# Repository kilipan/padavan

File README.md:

# Padavan
A Minivan keyboard with small numpad and wireless capabilities.

## Layout Options

An untested southpaw variant can be found in the [`southpaw`](https://github.com/kilipan/padavan/tree/main/southpaw) directory. Use at your own risk!

## BOM
| Amount | Part |
|-------:|:-----|
|      1 | Padavan PCB |
|      1 | Pro-Micro compatible MCU board |
|  58-63 | Kailh MX hot swap sockets |
|      1 | Padavan case and plate |
|     10 | Cylindrical magnets (d=3mm, l=2mm) |
|      5 | M2 screws, l=8mm |
|     11 | M2 screws, l=6mm |
|     16 | M2 heat inserts |

If you want to use the Padavan wirelessly, you'll need a wireless-capable controller, like e.g. the [nice!nano](https://nicekeyboards.com/nice-nano/)!

## Firmware
Tested and working [ZMK firmware](https://github.com/kilipan/zmk-config-padavan) is available,
as well as [QMK firmware including Vial](https://github.com/kilipan/qmk-config-padavan).

## Availability
All files are provided under CERN-OHL-S license. Feel free to build your own!

### Case
The fantastic case was designed by DizzySkizzo (`dizzyskizzo1337` on discord). Thank you for letting me use and open source this genius design!
Production files available in [`production/case`](https://github.com/kilipan/padavan/tree/main/production/case).

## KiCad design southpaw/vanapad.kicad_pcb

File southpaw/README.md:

# Vanapad
A southpaw Minivan keyboard with small numpad and wireless capabilities.

**Untested hardware! Use at your own risk!**

## Layout Options

## BOM
| Amount | Part |
|-------:|:-----|
|      1 | Vanapad PCB |
|      1 | Vanapad plate |
|      1 | Pro-Micro compatible MCU board |
|  58-63 | Kailh MX hot swap sockets |

If you want to use the Vanapad wirelessly, you'll need a wireless-capable controller, like e.g. the [nice!nano](https://nicekeyboards.com/nice-nano/)!

## Firmware
Not yet available. You can try modifying the padavan firmware!

## Availability
All files are provided under CERN-OHL-S license. Feel free to build your own!

### Case
None available as of the time of writing.

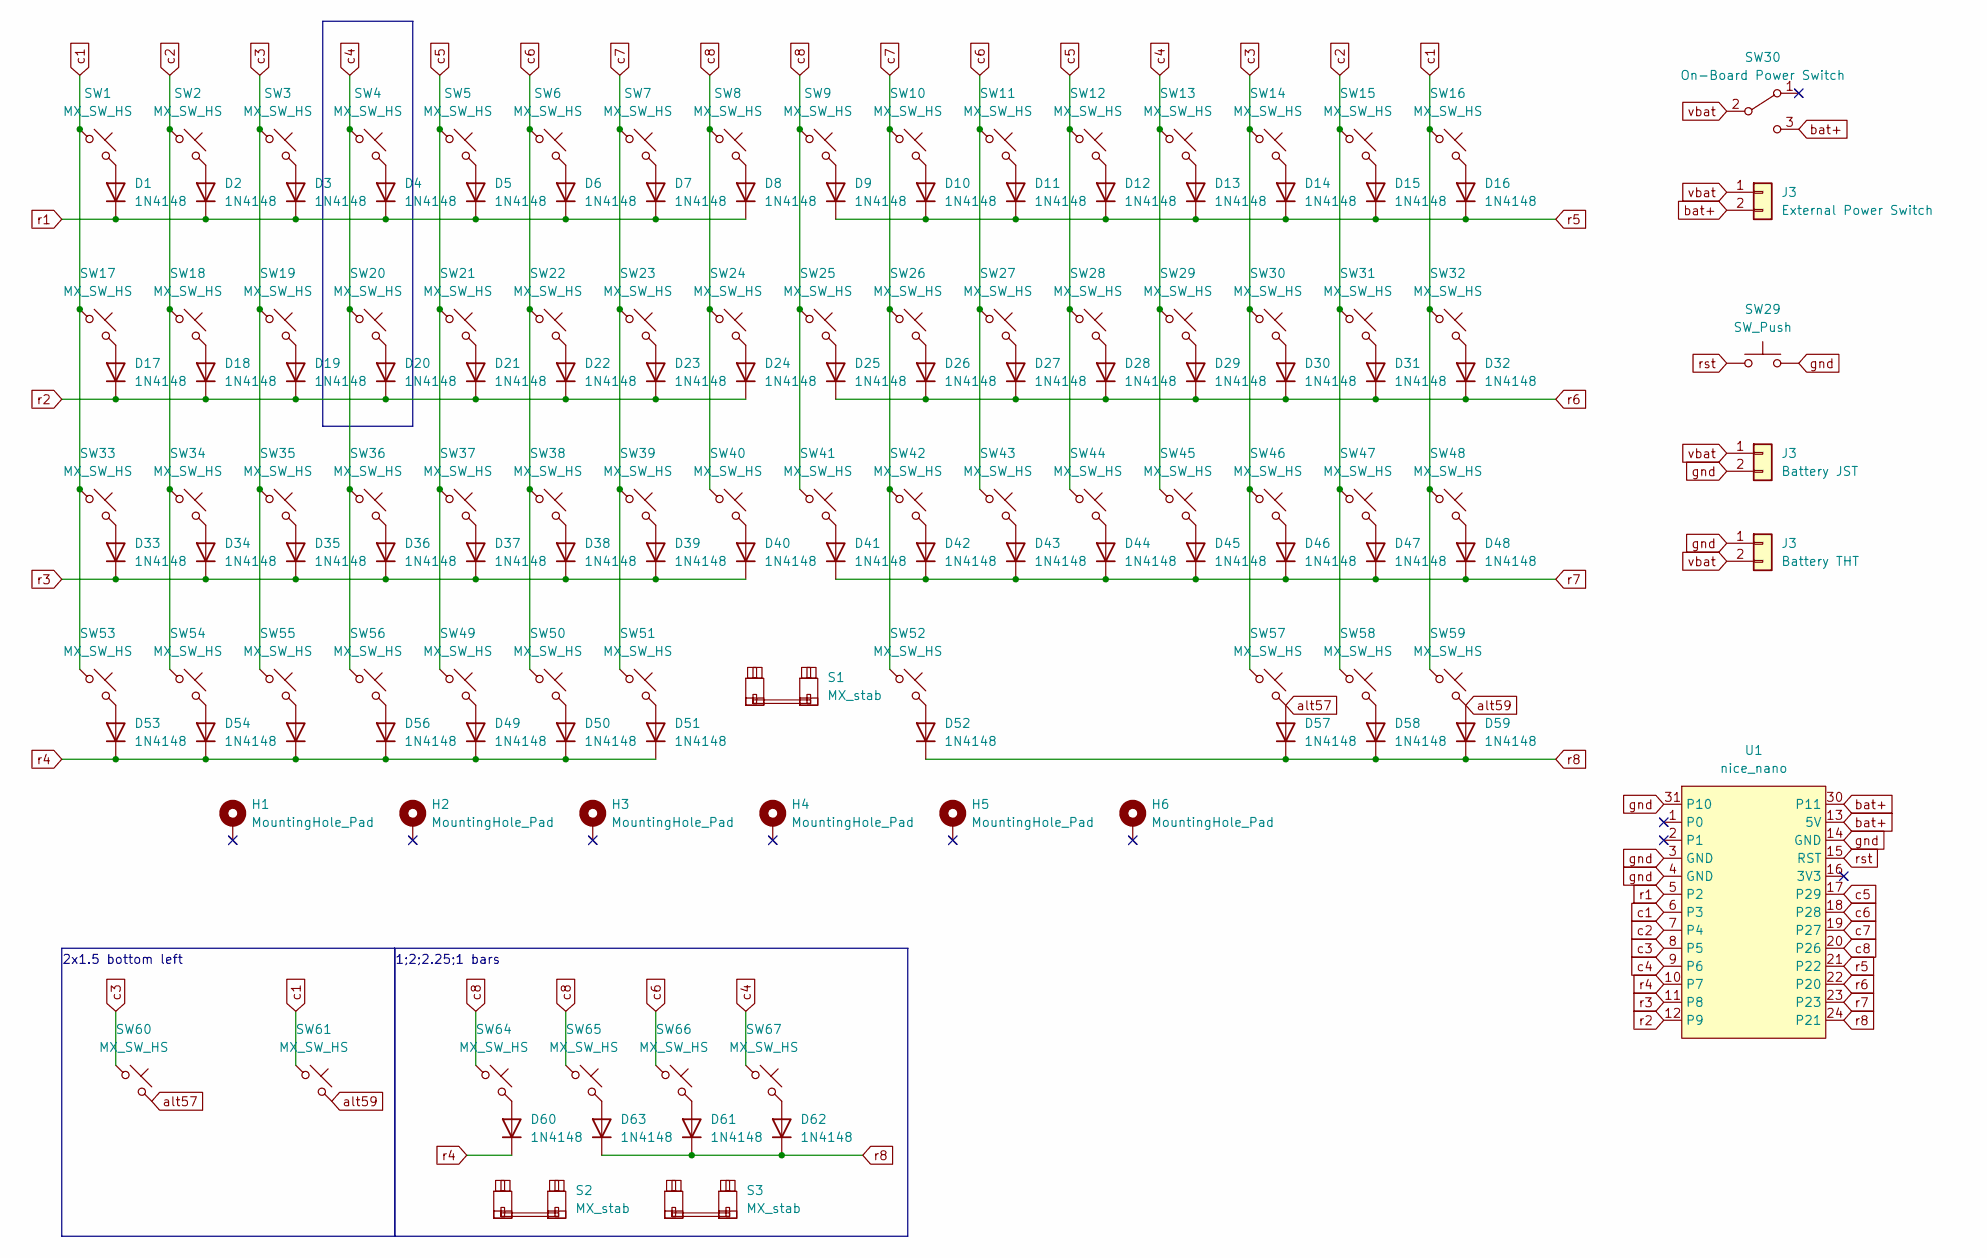
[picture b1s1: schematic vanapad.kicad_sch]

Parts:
D1, D2, D3, D4, D5, D6, D7, D8, D9, D10, D11, D12, D13, D14, D15, D16, D17, D18, D19, D20, D21, D22, D23, D24, D25, D26, D27, D28, D29, D30, D31, D32, D33, D34, D35, D36, D37, D38, D39, D40, D41, D42, D43, D44, D45, D46, D47, D48, D49, D50, D51, D52, D53, D54, D55, D56, D57, D58, D59, D60, D61, D62, D63: 1N4148; D_1206_3216Metric_Pad1.42x1.75mm_HandSolder
H1, H2, H3, H4, H5, H6: MountingHole_Pad; MountingHole_2.2mm_M2_Pad
J3: External Power Switch; power-switch_thts
S1: MX_stab; STAB_MX_P_6.25u
S2: MX_stab; STAB_MX_P_2u
S3: MX_stab; STAB_MX_P_2.25u
SW1, SW2, SW3, SW5, SW6, SW7, SW8, SW9, SW10, SW11, SW12, SW13, SW14, SW15, SW17, SW18, SW19, SW22, SW23, SW24, SW25, SW26, SW27, SW28, SW29, SW31, SW33, SW34, SW35, SW36, SW38, SW39, SW40, SW41, SW42, SW43, SW44, SW45, SW46, SW47, SW48, SW49, SW50, SW51, SW52, SW53, SW54, SW55, SW56, SW57, SW58, SW59, SW64, SW65, SW66, SW67: MX_SW_HS; SW_MX_HS_1u
SW4, SW20: MX_SW_HS; SW_MX_1u
SW16, SW37: MX_SW_HS; SW_MX_HS_1.75u
SW21: MX_SW_HS; SW_MX_HS_1.25u
SW30: On-Board Power Switch; SW_SPDT_PCM12
SW32: MX_SW_HS; SW_MX_HS_1.5u
SW60, SW61: MX_SW_HS; SW_MX_HS_CPG151101S11_1.5u
U1: nice_nano; nice_nano_AH_USBup

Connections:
unnamed: D1.2 (A), SW1.2
unnamed: D2.2 (A), SW2.2
unnamed: D3.2 (A), SW3.2
unnamed: D4.2 (A), SW4.2
unnamed: D5.2 (A), SW5.2
unnamed: D6.2 (A), SW6.2
unnamed: D7.2 (A), SW7.2
unnamed: D8.2 (A), SW8.2
unnamed: D9.2 (A), SW9.2
unnamed: D10.2 (A), SW10.2
unnamed: D11.2 (A), SW11.2
unnamed: D12.2 (A), SW12.2
unnamed: D13.2 (A), SW13.2
unnamed: D14.2 (A), SW14.2
unnamed: D15.2 (A), SW15.2
unnamed: D16.2 (A), SW16.2
unnamed: D17.2 (A), SW17.2
unnamed: D18.2 (A), SW18.2
unnamed: D19.2 (A), SW19.2
unnamed: D20.2 (A), SW20.2
unnamed: D21.2 (A), SW21.2
unnamed: D22.2 (A), SW22.2
unnamed: D23.2 (A), SW23.2
unnamed: D24.2 (A), SW24.2
unnamed: D25.2 (A), SW25.2
unnamed: D26.2 (A), SW26.2
unnamed: D27.2 (A), SW27.2
unnamed: D28.2 (A), SW28.2
unnamed: D31.2 (A), SW31.2
unnamed: D32.2 (A), SW32.2
unnamed: D33.2 (A), SW33.2
unnamed: D34.2 (A), SW34.2
unnamed: D35.2 (A), SW35.2
unnamed: D36.2 (A), SW36.2
unnamed: D37.2 (A), SW37.2
unnamed: D38.2 (A), SW38.2
unnamed: D39.2 (A), SW39.2
unnamed: D40.2 (A), SW40.2
unnamed: D41.2 (A), SW41.2
unnamed: D42.2 (A), SW42.2
unnamed: D43.2 (A), SW43.2
unnamed: D44.2 (A), SW44.2
unnamed: D45.2 (A), SW45.2
unnamed: D46.2 (A), SW46.2
unnamed: D47.2 (A), SW47.2
unnamed: D48.2 (A), SW48.2
unnamed: D49.2 (A), SW49.2
unnamed: D50.2 (A), SW50.2
unnamed: D51.2 (A), SW51.2
unnamed: D52.2 (A), SW52.2
unnamed: D53.2 (A), SW53.2
unnamed: D54.2 (A), SW54.2
unnamed: D55.2 (A), SW55.2
unnamed: D56.2 (A), SW56.2
unnamed: D58.2 (A), SW58.2
unnamed: D60.2 (A), SW64.2
unnamed: D61.2 (A), SW66.2
unnamed: D62.2 (A), SW67.2
unnamed: D63.2 (A), SW65.2
alt57: D57.2 (A), SW57.2, SW60.2
alt59: D59.2 (A), SW59.2, SW61.2
c1: SW1.1, SW16.1, SW17.1, SW32.1, SW33.1, SW48.1, SW53.1, SW59.1, SW61.1, U1.6 (P3)
c2: SW2.1, SW15.1, SW18.1, SW31.1, SW34.1, SW47.1, SW54.1, SW58.1, U1.7 (P4)
c3: SW3.1, SW14.1, SW19.1, SW30.1, SW35.1, SW46.1, SW55.1, SW57.1, SW60.1, U1.8 (P5)
c5: SW5.1, SW12.1, SW21.1, SW28.1, SW37.1, SW44.1, SW49.1, U1.17 (P29)
c6: SW6.1, SW11.1, SW22.1, SW27.1, SW38.1, SW43.1, SW50.1, SW66.1, U1.18 (P28)
c7: SW7.1, SW10.1, SW23.1, SW26.1, SW39.1, SW42.1, SW51.1, SW52.1, U1.19 (P27)
c8: SW8.1, SW9.1, SW24.1, SW25.1, SW40.1, SW41.1, SW64.1, SW65.1, U1.20 (P26)
r1: D1.1 (K), D2.1 (K), D3.1 (K), D4.1 (K), D5.1 (K), D6.1 (K), D7.1 (K), D8.1 (K), U1.5 (P2)
r2: D17.1 (K), D18.1 (K), D19.1 (K), D20.1 (K), D21.1 (K), D22.1 (K), D23.1 (K), D24.1 (K), U1.12 (P9)
r3: D33.1 (K), D34.1 (K), D35.1 (K), D36.1 (K), D37.1 (K), D38.1 (K), D39.1 (K), D40.1 (K), U1.11 (P8)
r4: D49.1 (K), D50.1 (K), D51.1 (K), D53.1 (K), D54.1 (K), D55.1 (K), D56.1 (K), D60.1 (K), U1.10 (P7)
r5: D9.1 (K), D10.1 (K), D11.1 (K), D12.1 (K), D13.1 (K), D14.1 (K), D15.1 (K), D16.1 (K), U1.21 (P22)
r6: D25.1 (K), D26.1 (K), D27.1 (K), D28.1 (K), D29.1 (K), D30.1 (K), D31.1 (K), D32.1 (K), U1.22 (P20)
r7: D41.1 (K), D42.1 (K), D43.1 (K), D44.1 (K), D45.1 (K), D46.1 (K), D47.1 (K), D48.1 (K), U1.23
r8: D52.1 (K), D57.1 (K), D58.1 (K), D59.1 (K), D61.1 (K), D62.1 (K), D63.1 (K), U1.24 (P21)

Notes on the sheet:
1;2;2.25;1 bars
2x1.5 bottom left

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
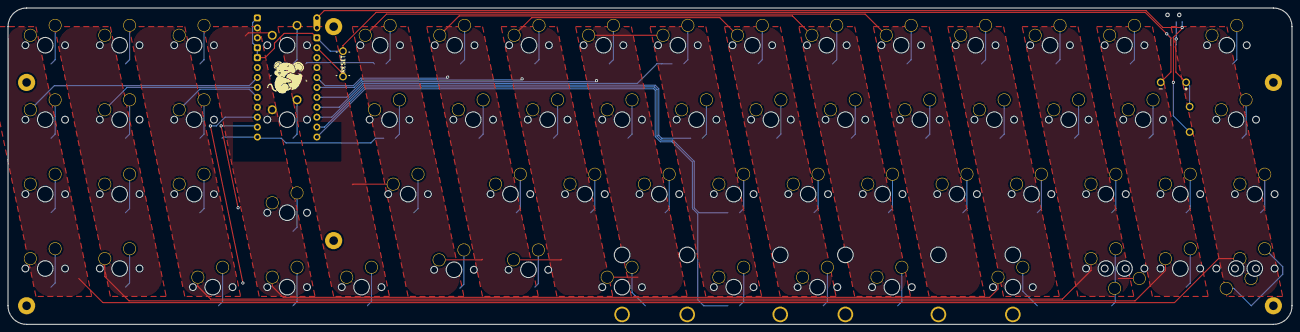
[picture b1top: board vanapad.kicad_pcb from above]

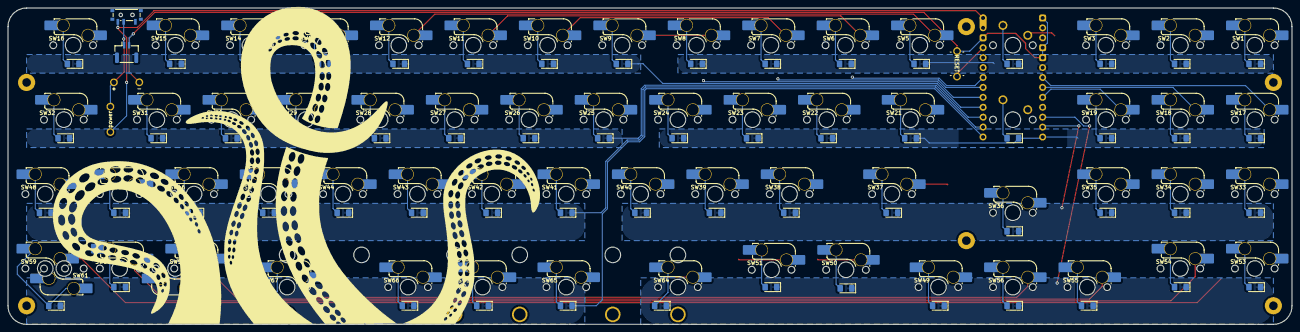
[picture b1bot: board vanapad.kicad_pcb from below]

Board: 2 copper layers, 328.6 x 81.0 mm, 143 parts (131 on the bottom side), 83 nets.

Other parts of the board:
J1: Battery JST; JST_GH_SM02B-GHS-TB_1x02-1MP_P1.25mm_Horizontal
J2: External Power Switch; power-switch_thts
SW62: On-Board Power Switch; SW_SPDT_PCM12
SW63: SW_Push; SW_ResetSW

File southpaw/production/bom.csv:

Designator,Footprint,Quantity,Value,LCSC Part #
"D1, D10, D11, D12, D13, D14, D15, D16, D17, D18, D19, D2, D20, D21, D22, D23, D24, D25, D26, D27, D28, D29, D3, D30, D31, D32, D33, D34, D35, D36, D37, D38, D39, D4, D40, D41, D42, D43, D44, D45, D46, D47, D48, D49, D5, D50, D51, D52, D53, D54, D55, D56, D57, D58, D59, D6, D60, D61, D62, D63, D7, D8, D9",1206,63,1N4148,
"H1, H2, H3, H4, H5, H6",MountingHole_2.2mm_M2_Pad,6,MountingHole_Pad,
J1,JST_GH_SM02B-GHS-TB_1x02-1MP_P1.25mm_Horizontal,1,Battery JST,
J2,power-switch_thts,1,External Power Switch,
J3,power-thts,1,Battery THT,
S1,STAB_MX_P_6.25u,1,MX_stab,
S2,STAB_MX_P_2u,1,MX_stab,
S3,STAB_MX_P_2.25u,1,MX_stab,
"SW1, SW10, SW11, SW12, SW13, SW14, SW15, SW17, SW18, SW19, SW2, SW22, SW23, SW24, SW25, SW26, SW27, SW28, SW29, SW3, SW30, SW31, SW33, SW34, SW35, SW36, SW38, SW39, SW40, SW41, SW42, SW43, SW44, SW45, SW46, SW47, SW48, SW49, SW5, SW50, SW51, SW52, SW53, SW54, SW55, SW56, SW57, SW58, SW59, SW6, SW64, SW65, SW66, SW67, SW7, SW8, SW9",SW_MX_HS_1u,57,MX_SW_HS,
"SW16, SW37",SW_MX_HS_1.75u,2,MX_SW_HS,
"SW20, SW4",SW_MX_1u,2,MX_SW_HS,
SW21,SW_MX_HS_1.25u,1,MX_SW_HS,
SW32,SW_MX_HS_1.5u,1,MX_SW_HS,
"SW60, SW61",SW_MX_HS_CPG151101S11_1.5u,2,MX_SW_HS,
SW62,SW_SPDT_PCM12,1,On-Board Power Switch,
SW63,SW_ResetSW,1,SW_Push,
U1,nice_nano_AH_USBup,1,nice_nano,

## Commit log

2024-02-28 add photo
2024-02-28 provide unzipped case files
2025-02-28 add untested vanapad files
2025-02-28 remove unnecessary jj repo
2025-02-28 fix alternative bottom row routing
2025-02-28 make vanapad pcb compatible with mirrored case
2025-06-06 fix: correct qmk fw link
2025-06-06 feat: add case hardware to BOM
2025-06-06 fix: replace 'padavan'by 'vanapad' where applicable
2025-06-10 feat: add vanapad plate
